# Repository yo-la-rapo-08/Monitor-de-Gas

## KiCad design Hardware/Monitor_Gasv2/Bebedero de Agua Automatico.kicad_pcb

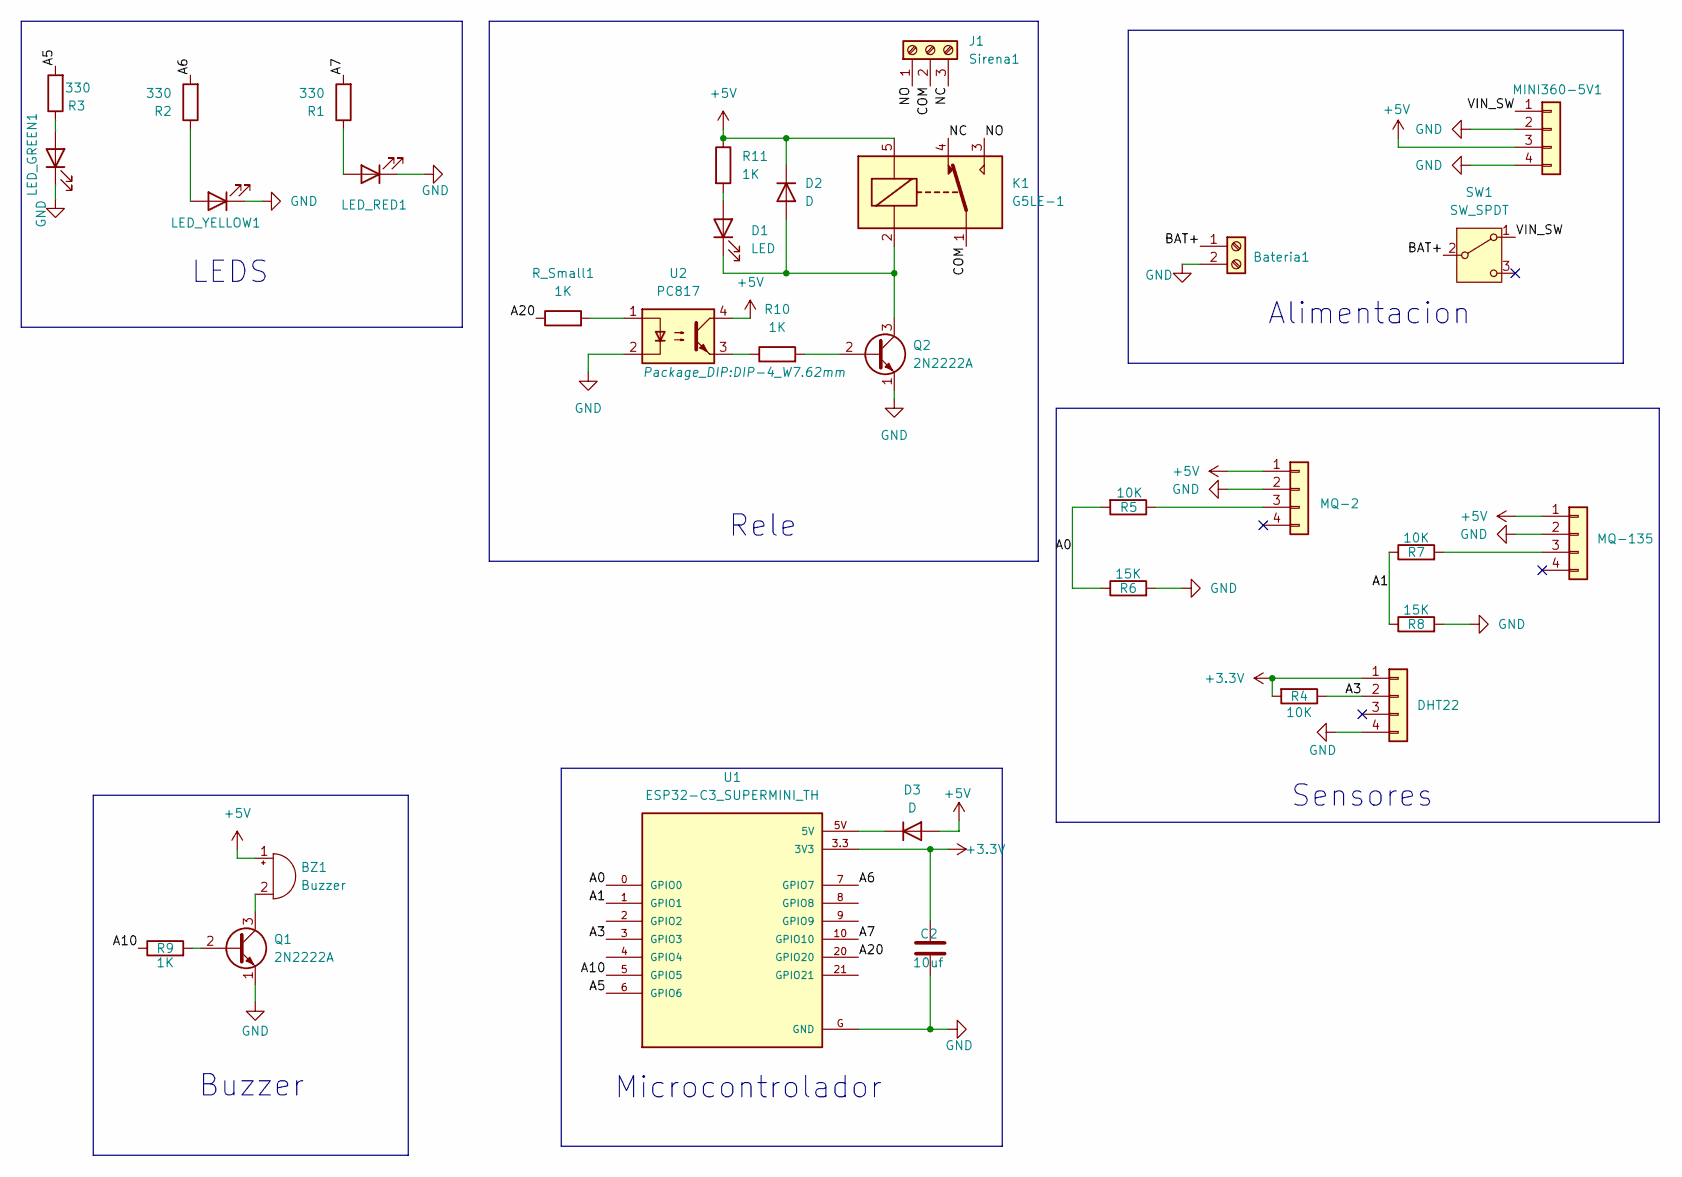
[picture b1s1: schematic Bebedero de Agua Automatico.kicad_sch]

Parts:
BZ1: Buzzer; Buzzer_12x9.5RM7.6
Bateria1: TerminalBlock_bornier-2_P5.08mm
C2: 10uf; C_0805_2012Metric
D1: LED; LED_0805_2012Metric
D2, D3: D; D_SMA
DHT22: ASAIR_AM2302_P2.54mm_Vertical
J1: Sirena1; TerminalBlock_Phoenix_MKDS-1,5-3-5.08_1x03_P5.08mm_Horizont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
K1: G5LE-1; Relay_SPDT_SANYOU_SRD_Series_Form_C
LED_GREEN1: LED_D5.0mm
LED_RED1: LED_D5.0mm
LED_YELLOW1: LED_D5.0mm
MINI360-5V1: Mini360
MQ-2: Conn_01x04; PinHeader_1x04_P2.54mm_Vertical
MQ-135: PinHeader_1x04_P2.54mm_Vertical
Q1, Q2: 2N2222A; TO-92_Inline
R1, R2, R3: 330; R_0805_2012Metric
R4, R5, R7: 10K; R_0805_2012Metric
R6, R8: 15K; R_0805_2012Metric
R9, R10, R11: 1K; R_0805_2012Metric
R_Small1: 1K; R_0805_2012Metric
SW1: SW_SPDT; PinHeader_1x03_P2.54mm_Vertical
U1: ESP32-C3_SUPERMINI_TH; MODULE_ESP32-C3_SUPERMINI
U2: PC817; DIP-4_W7.62mm

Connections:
+3.3V: C2.1, DHT22.1, R4.2, U1.3.3 (3V3)
+5V: BZ1.1 (+), D2.1 (K), D3.2 (A), K1.5, MINI360-5V1.3, MQ-2.1, MQ-135.1, R11.1, U2.4
/A0: R5.2, R6.1, U1.0 (GPIO0)
/A1: R7.1, R8.1, U1.1 (GPIO1)
/A3: DHT22.2, R4.1, U1.3 (GPIO3)
/A5: R3.2, U1.6 (GPIO6)
/A6: R2.2, U1.7 (GPIO7)
/A7: R1.2, U1.10 (GPIO10)
/A10: R9.1, U1.5 (GPIO5)
/A20: R_Small1.1, U1.20 (GPIO20)
/BAT+: Bateria1.1, SW1.2 (B)
/COM: J1.2, K1.1
/NC: J1.3, K1.4
/NO: J1.1, K1.3
/VIN_SW: MINI360-5V1.1, SW1.1 (A)
GND: Bateria1.2, C2.2, DHT22.4, LED_GREEN1.1 (K), LED_RED1.1 (K), LED_YELLOW1.1 (K), MINI360-5V1.2, MINI360-5V1.4, MQ-2.2, MQ-135.2, Q1.1 (E), Q2.1 (E), R6.2, R8.2, U1.G (GND), U2.2
unnamed: BZ1.2 (-), Q1.3 (C)
unnamed: D1.2 (A), R11.2
unnamed: D1.1 (K), D2.2 (A), K1.2, Q2.3 (C)
unnamed: D3.1 (K), U1.5V
unnamed: LED_GREEN1.2 (A), R3.1
unnamed: LED_RED1.2 (A), R1.1
unnamed: LED_YELLOW1.2 (A), R2.1
unnamed: MQ-2.3, R5.1
unnamed: MQ-135.3, R7.2
unnamed: Q1.2 (B), R9.2
unnamed: Q2.2 (B), R10.2
unnamed: R10.1, U2.3
unnamed: R_Small1.2, U2.1

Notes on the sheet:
Alimentacion
Microcontrolador
Rele
Sensores
Buzzer
LEDS

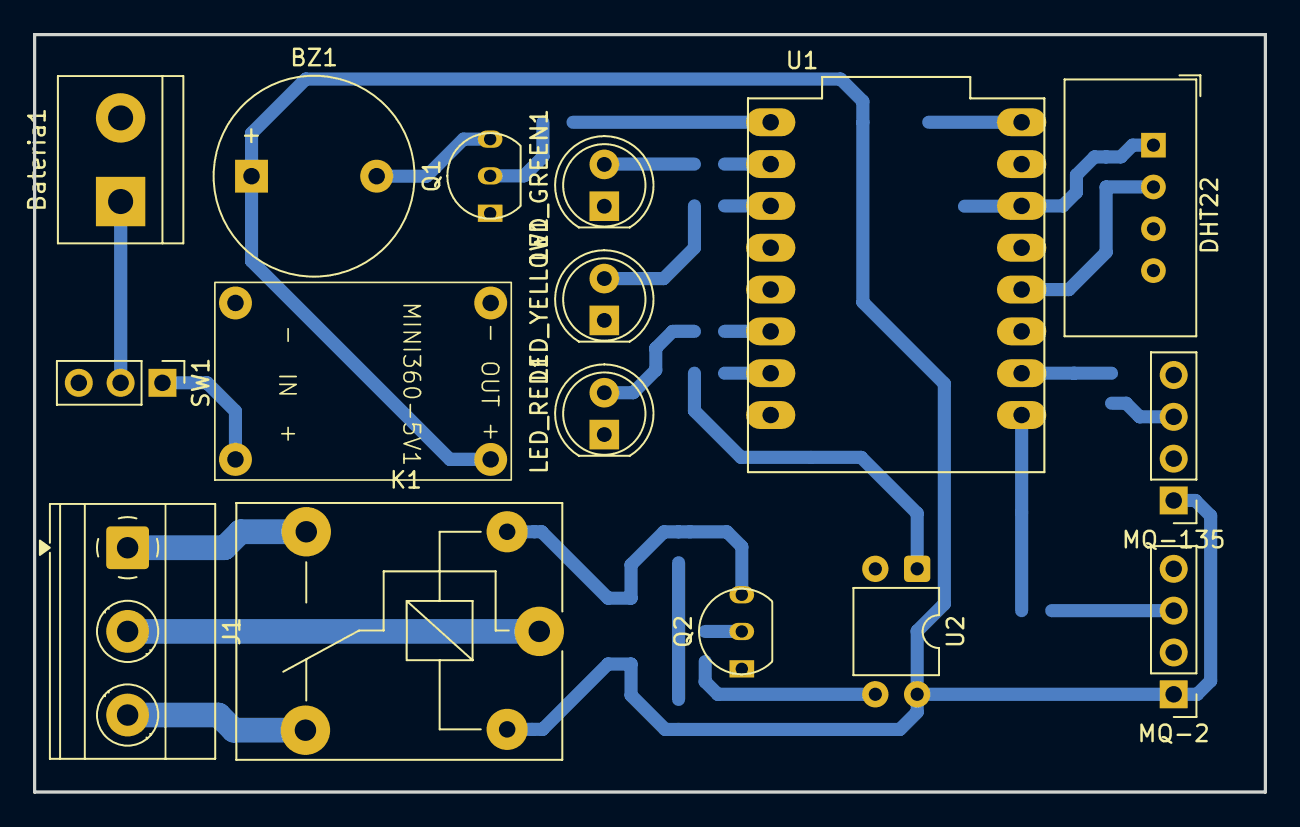
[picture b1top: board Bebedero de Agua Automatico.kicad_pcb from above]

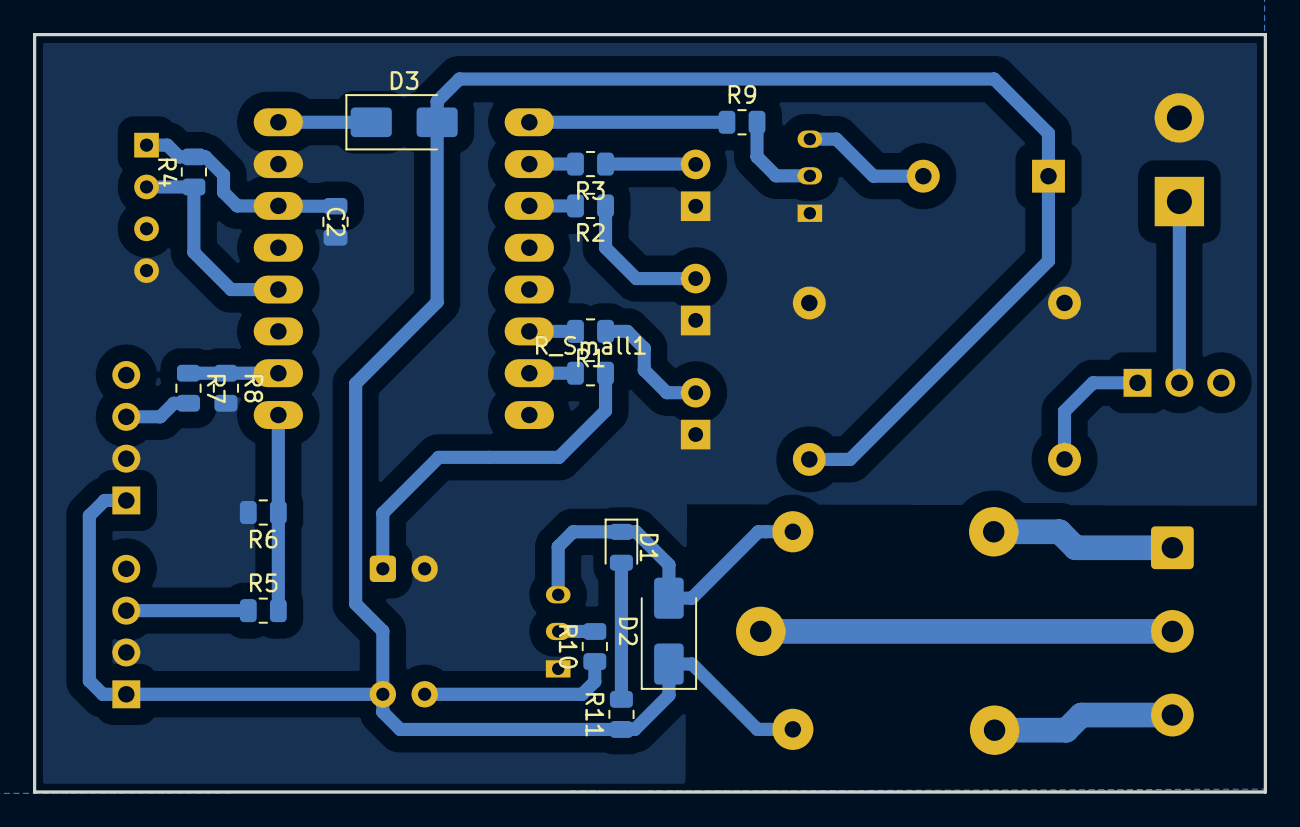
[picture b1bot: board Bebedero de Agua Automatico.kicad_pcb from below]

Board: 2 copper layers, 74.8 x 46.0 mm, 32 parts (16 on the bottom side), 29 nets.
